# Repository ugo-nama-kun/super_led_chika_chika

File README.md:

# Super LED Chika Chika

LED をチカチカするだけのものをハードウェア制作の練習に作ったときの成果物

### 部品（秋月電子で全て購入）
* カーボン抵抗：330Ω, スルーホール, 5%, 1/4W：https://akizukidenshi.com/catalog/g/gR-25331/
* タクトスイッチ, スルーホール：https://akizukidenshi.com/catalog/g/gP-03647/
* 緑色LED, スルーホール：https://akizukidenshi.com/catalog/g/gI-12606/
* 積層セラミックコンデンサ, 0.1uF, スルーホール：https://akizukidenshi.com/catalog/g/gP-00090/

### 使用機材・ソフトなど
* KiCad (基板データ)
* Fusion 360 (箱のモデリング)
* FLASH FORGE Finder (3Dプリンタ)
* はんだごて
* JLCPCB (基板作成業者様)

### 参考サイト様など
* 超Lチカ団（KiCad）: https://youtu.be/dNfaLM5PUVM
* ZEPエンジニアリング(KiCadのフットプリント関係)：https://www.zep.co.jp/nbeppu/article/z-kicad-da3/
* 自作キーボード温泉街の歩き方（発注関係）：https://salicylic-acid3.hatenablog.com/entry/jlcpcb-order

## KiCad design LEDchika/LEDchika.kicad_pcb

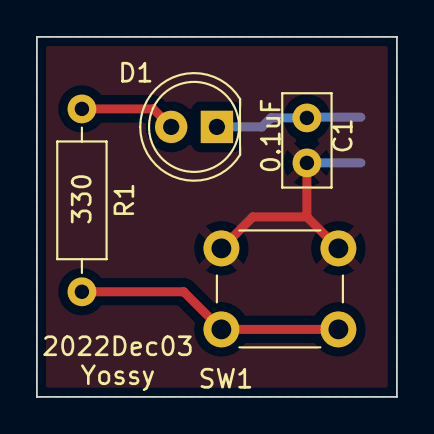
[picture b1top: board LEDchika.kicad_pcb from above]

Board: 2 copper layers, 20.0 x 20.0 mm, 5 parts (1 on the bottom side), 4 nets.

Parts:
C1: 0.1u; C_Disc_D5.0mm_W2.5mm_P2.50mm
D1: LED; LED_D5.0mm
J1: Source; Pad_01x02_SMD
R1: 330; R_Axial_DIN0207_L6.3mm_D2.5mm_P10.16mm_Horizontal
SW1: SW_Push; SW_PUSH_6mm

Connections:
+5V: C1.1, J1.2, SW1.2
GND: C1.2, D1.1 (K), J1.1
unnamed: D1.2 (A), R1.1
unnamed: R1.2, SW1.1
